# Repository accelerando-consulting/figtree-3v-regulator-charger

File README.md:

# Figtree - a simple battery maintenance board

This board takes in 4-6v from USB, solar panel or other DC, and charges a lithium battery.

It also delivers regulated 3.3v at up to 600mA.

Basically it is an all in one "Run a microcontroller board off solar and/or battery" hack.

The board has three key connections

  * Charging power in
  * Battery in/out
  * Project power out

There are solder pads for wires, and JST connector footprints for each of these.   You can use one
or the other.

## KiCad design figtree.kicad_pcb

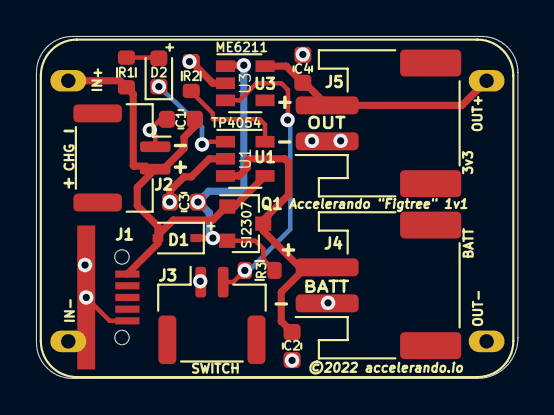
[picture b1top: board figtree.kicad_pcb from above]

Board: 2 copper layers, 26.8 x 19.0 mm, 18 parts (0 on the bottom side), 9 nets.

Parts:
C1, C2: 10uF; C_0603_1608Metric
C3, C4: 100nF; C_0603_1608Metric
D1: B320A; D_SOD-323
D2: LED 0603 RED; LED_0603_1608Metric
J1: USB_B_Micro; USB_Micro_SMD
J2: CHG; JST_GH_SM02B-GHS-TB_1x02-1MP_P1.25mm_Horizontal
J3: Off; JST_GH_SM02B-GHS-TB_1x02-1MP_P1.25mm_Horizontal
J4: Batt; JST_PH_S2B-PH-SM4-TB_1x02-1MP_P2.00mm_Horizontal
J5: OUT; JST_PH_S2B-PH-SM4-TB_1x02-1MP_P2.00mm_Horizontal
Q1: SI2307; SOT-23
R1, R2: 2k; R_0603_1608Metric
R3: 10k; R_0603_1608Metric
U1: TP4054; SOT-23-5
U2: BUCKBOOST
U3: ME6211; SOT-23-5

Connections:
+BATT: C2.1, J4.2, Q1.3 (D), U1.3 (BAT)
/5v: C3.1, D1.1 (K), Q1.2 (S), R3.2, U3.1 (VIN)
/CE: J3.2, R3.1, U3.3 (CE)
/CHRG: D2.1 (K), U1.1 (~CHRG)
/D3+: D2.2 (A), R1.2
/PROG: R2.1, U1.5 (PROG)
/VIN: C1.1, D1.2 (A), J1.1 (VBUS), J2.2, Q1.1 (G), R1.1, U1.4 (Vcc), U2.1 (IN+)
/VOUT: C4.1, J5.2, U2.4 (OUT+), U3.5 (VOUT)
GND: C1.2, C2.2, C3.2, C4.2, J1.5 (GND), J1.6 (Shield), J2.1, J3.1, J4.1, J5.1, R2.2, U1.2 (GND), U2.2 (IN-), U2.3 (OUT-), U3.2 (GND)

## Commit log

2022-04-12 Buckbatt module, millable power supply
2026-03-03 Rename to figtree
2026-03-03 Add panelised board
2026-03-03 Update PCB for rename
2026-03-03 Add images for 1v1
2026-03-03 Update png and pdfs
2026-03-03 UBLC
2026-03-03 README.md - Add more doco
2026-03-03 Add photograph of board in use
2026-03-03 README.md - relocate photo

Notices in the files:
figtree.kicad_pcb:
©2022 accelerando.io
